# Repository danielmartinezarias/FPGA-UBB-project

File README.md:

# FPGA UBB Quantum Optics Lab
FPGA project for the control system of the OAM experiment. FPGA stores a set of images in a DDR memory, displays such images via HDMI port, prepares a train of short pulses to drive an EOM Intensity modulator, and aquires counts from 2 detectors. This project is meant to work along a GUI written in C#.

1. **electronics** contains the source files for the FMC PCB and the LM7171 AMP PCB. These includes manufacturing files, schematics and PCB outlines
2. **caja** contains a blender file with the mechanical drawings of the plastic box for the project
3. **Figuras_Hologramas_OAM** contains a set of holograms to display, and some images with numbers for calibration
4. **FPGA-Vivado-Project** contains the main Vivado project in `Genesys2_VideoDemoR1` and its sources in `srcs`. You can use the project as it is ot build the project by your own running the *srcs/Genesys2_VideoDemoR1.tcl* file with their respective dependencies and then build your own project. Synthesis, implementation and bitstream generation
5. **GUI** includes the main Graphical User Interface (GUI) to run the program along with the FPGA project. C# project in `SOFTWARE BASE-UART` and final GUI in `FINAL`. Notice that a USB UART connection is required to transmit information from the FPGA to PC 115200 buad rate.

## GUI
C# project in `GUI\SOFTWARE BASE-UART\` and FINAL Graphical User  Interface (GUI), located in `GUI\SOFTWARE BASE-UART\driver_PM_software\bin\Debug\driver_PM_software.exe`
**GUI controls**
- SOON TO BE UPDATED

## FPGA
- Main Vivado project in `FPGA-Vivado-Project\Genesys2_VideoDemoR1`, 
    - Final bitstream is located in `FPGA-Vivado-Project\Genesys2_VideoDemoR1\Genesys2_VideoDemoR1.runs\impl_1\*.bit`. 
    - You can upload this file into the FPGA using Vivado. Left bottom menu, PROGRAM AND DEBUG, Open Hardware, Auto connect, Program FPGA (with the .bit file)
- `srcs` contains all verilog files, please keep this updated

### How to use this repo?
- Create a GitHub account
- Download Github desktop
- CLONE the repository (ask me for access since it is a private repo)
    - If you want to use this files and not modify them CLONE this repository in the MAIN branch. 
    - If you want to modify it create a new branch and have fun
- Now all the files are in the folder where you cloned the repo.
- If you want to make permanet changes to the MAIN branch, make a commit, but ask me first
- GitHub is not meant to store experiment data, but code, keep this repo as clean as possible.

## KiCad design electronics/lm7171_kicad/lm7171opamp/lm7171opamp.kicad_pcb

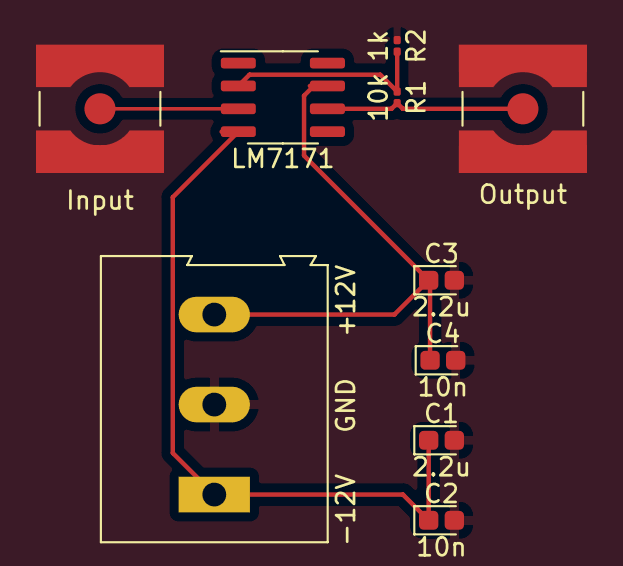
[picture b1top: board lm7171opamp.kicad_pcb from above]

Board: 2 copper layers, 10 parts (0 on the bottom side), 6 nets.

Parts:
C1, C3: 2.2u; CP_EIA-1608-08_AVX-J
C2, C4: 10n; CP_EIA-1608-08_AVX-J
J1: Input; SMA_Amphenol_132134-10_Vertical
J2: Output; SMA_Amphenol_132134-10_Vertical
J3: -12V GND +12V; TerminalBlock_Altech_AK300-3_P5.00mm
R1: 10k; R_0201_0603Metric
R2: 1k; R_0201_0603Metric
U1: LM7171; SOIC-8_3.9x4.9mm_P1.27mm

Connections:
GND: C1.2, C2.2, C3.2, C4.2, J1.2 (Ext), J2.2 (Ext), J3.2, R2.1
unnamed: J1.1 (In), U1.3 (+)
unnamed: J2.1 (In), R1.2, U1.6
unnamed: C1.1, C2.1, J3.1, U1.4 (V-)
unnamed: C3.1, C4.1, J3.3, U1.7 (V+)
unnamed: R1.1, R2.2, U1.2 (-)

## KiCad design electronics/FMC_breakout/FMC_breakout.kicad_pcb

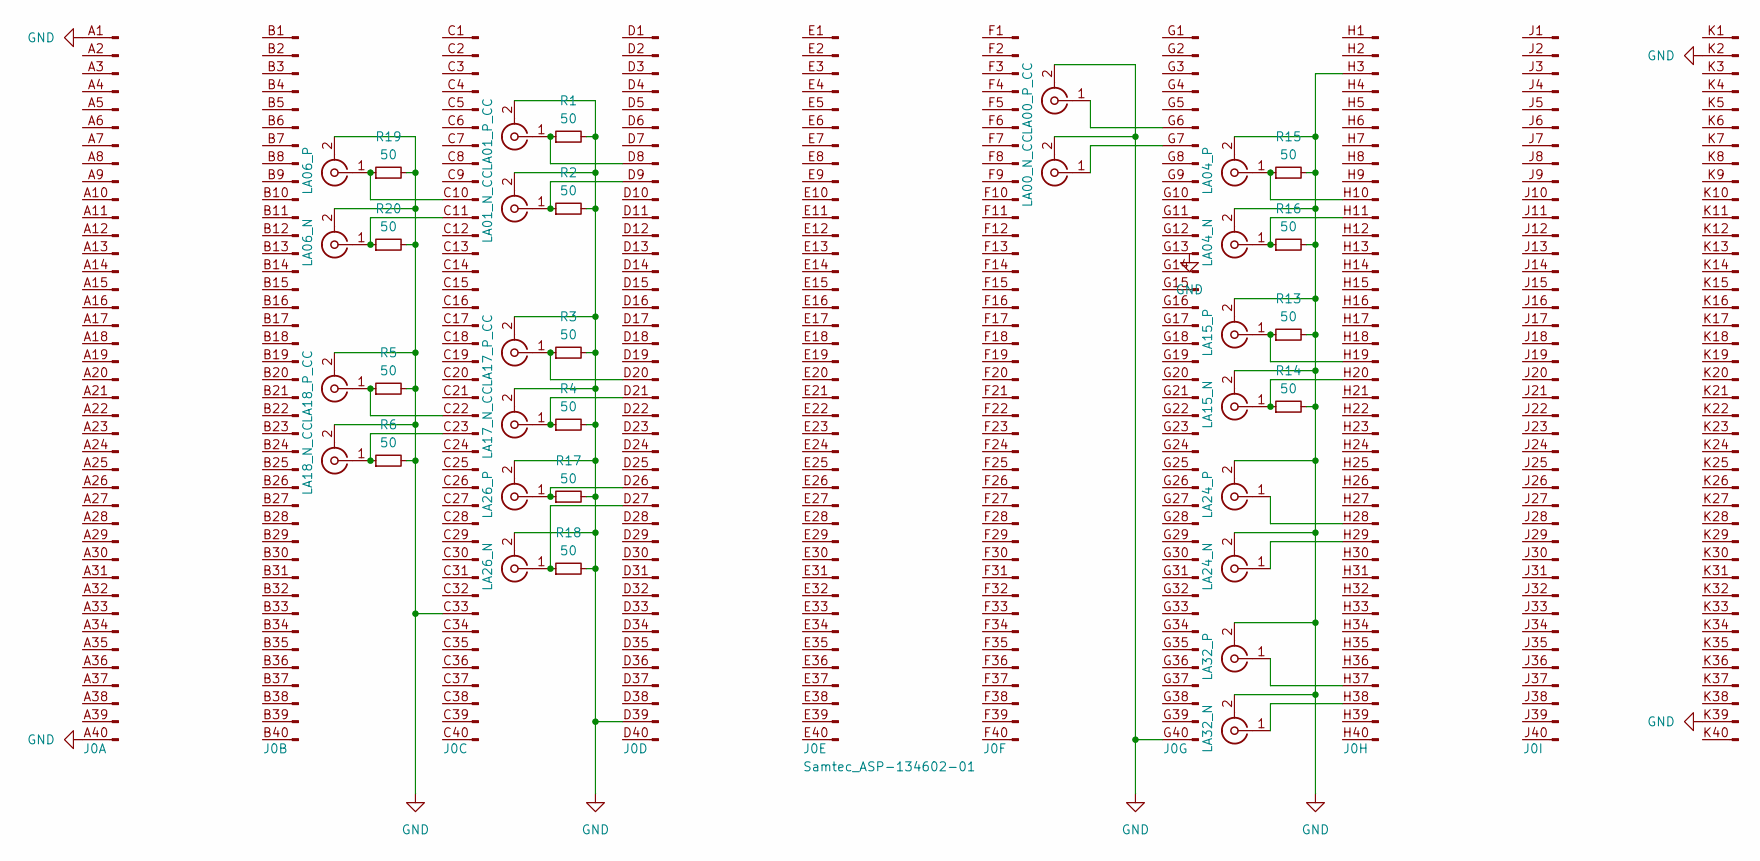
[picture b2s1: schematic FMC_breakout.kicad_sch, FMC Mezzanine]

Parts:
J0: Samtec_ASP-134602-01; Samtec_FMC_ASP-134602-01_10x40_P1.27mm_Vertical; LCSC C2875619
J1: LA01_P_CC; U.FL_Hirose_U.FL-R-SMT-1_Vertical
J2: LA01_N_CC; U.FL_Hirose_U.FL-R-SMT-1_Vertical
J3: LA17_P_CC; U.FL_Hirose_U.FL-R-SMT-1_Vertical
J4: LA17_N_CC; U.FL_Hirose_U.FL-R-SMT-1_Vertical
J5: LA18_P_CC; U.FL_Hirose_U.FL-R-SMT-1_Vertical
J6: LA18_N_CC; U.FL_Hirose_U.FL-R-SMT-1_Vertical
J7: LA00_P_CC; U.FL_Hirose_U.FL-R-SMT-1_Vertical
J8: LA00_N_CC; U.FL_Hirose_U.FL-R-SMT-1_Vertical
J9: LA32_P; U.FL_Hirose_U.FL-R-SMT-1_Vertical
J10: LA32_N; U.FL_Hirose_U.FL-R-SMT-1_Vertical
J11: LA24_P; U.FL_Hirose_U.FL-R-SMT-1_Vertical
J12: LA24_N; U.FL_Hirose_U.FL-R-SMT-1_Vertical
J13: LA15_P; U.FL_Hirose_U.FL-R-SMT-1_Vertical
J14: LA15_N; U.FL_Hirose_U.FL-R-SMT-1_Vertical
J15: LA04_P; U.FL_Hirose_U.FL-R-SMT-1_Vertical
J16: LA04_N; U.FL_Hirose_U.FL-R-SMT-1_Vertical
J17: LA26_P; U.FL_Hirose_U.FL-R-SMT-1_Vertical
J18: LA26_N; U.FL_Hirose_U.FL-R-SMT-1_Vertical
J19: LA06_P; U.FL_Hirose_U.FL-R-SMT-1_Vertical; LCSC C434812
J20: LA06_N; U.FL_Hirose_U.FL-R-SMT-1_Vertical
R1, R2, R3, R4, R5, R6, R13, R14, R15, R16, R17, R19, R20: 50; R_0402_1005Metric
R18: 50; R_0402_1005Metric; LCSC C853312

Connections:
GND: J0.A1 (Pin_1), J0.A40 (Pin_40), J0.C33 (Pin_33), J0.D39 (Pin_39), J0.G40 (Pin_40), J0.H3 (Pin_3), J0.K2 (Pin_2), J0.K39 (Pin_39), J1.2 (Ext), J2.2 (Ext), J3.2 (Ext), J4.2 (Ext), J5.2 (Ext), J6.2 (Ext), J7.2 (Ext), J8.2 (Ext), J9.2 (Ext), J10.2 (Ext), J11.2 (Ext), J12.2 (Ext), J13.2 (Ext), J14.2 (Ext), J15.2 (Ext), J16.2 (Ext), J17.2 (Ext), J18.2 (Ext), J19.2 (Ext), J20.2 (Ext), R1.2, R2.2, R3.2, R4.2, R5.2, R6.2, R13.2, R14.2, R15.2, R16.2, R17.2, R18.2, R19.2, R20.2
unnamed: J0.C10 (Pin_10), J19.1 (In), R19.1
unnamed: J0.C11 (Pin_11), J20.1 (In), R20.1
unnamed: J0.C22 (Pin_22), J5.1 (In), R5.1
unnamed: J0.C23 (Pin_23), J6.1 (In), R6.1
unnamed: J0.D8 (Pin_8), J1.1 (In), R1.1
unnamed: J0.D9 (Pin_9), J2.1 (In), R2.1
unnamed: J0.D20 (Pin_20), J3.1 (In), R3.1
unnamed: J0.D21 (Pin_21), J4.1 (In), R4.1
unnamed: J0.D26 (Pin_26), J17.1 (In), R17.1
unnamed: J0.D27 (Pin_27), J18.1 (In), R18.1
unnamed: J0.G6 (Pin_6), J7.1 (In)
unnamed: J0.G7 (Pin_7), J8.1 (In)
unnamed: J0.H10 (Pin_10), J15.1 (In), R15.1
unnamed: J0.H11 (Pin_11), J16.1 (In), R16.1
unnamed: J0.H19 (Pin_19), J13.1 (In), R13.1
unnamed: J0.H20 (Pin_20), J14.1 (In), R14.1
unnamed: J0.H28 (Pin_28), J11.1 (In)
unnamed: J0.H29 (Pin_29), J12.1 (In)
unnamed: J0.H37 (Pin_37), J9.1 (In)
unnamed: J0.H38 (Pin_38), J10.1 (In)

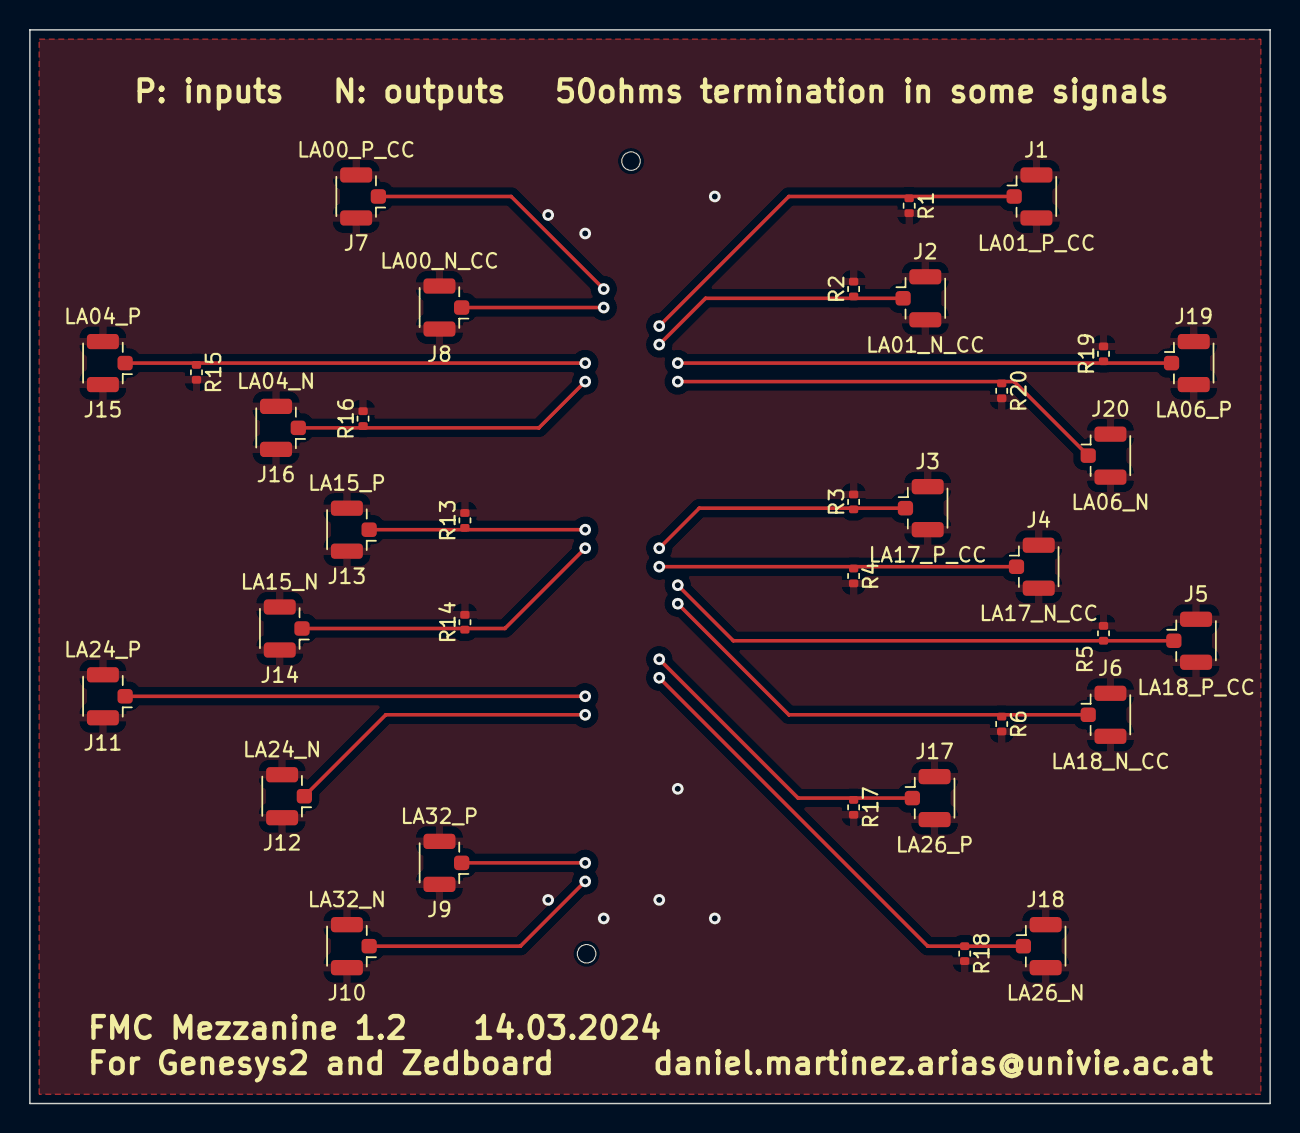
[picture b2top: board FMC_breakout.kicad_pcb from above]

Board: 2 copper layers, 85.1 x 73.7 mm, 35 parts (1 on the bottom side), 21 nets.

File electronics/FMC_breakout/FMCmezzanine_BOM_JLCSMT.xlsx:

Comment | Designator | Footprint | JLCPCB Part #（optional）
50ohm | R1,R2,R3,R4,R5,R6,R13,R14,R15,R16,R17,R18,R19,R20 | R_0402_1005Metric | C853312
 | J1,J2,J3,J4,J5,J6,J7,J8,J9,J10,J11,J12,J13,J14,J15,J16,J17,J18,J19,J20 | Connector_Coaxial:U.FL_Hirose_U.FL-R-SMT-1_Vertical | C434812
Samtec_ASP-134602-01 | J0 | Connector_Samtec:Samtec_FMC_ASP-134602-01_10x40_P1.27mm_Vertical | C2875619

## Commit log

2024-05-09 Initial project commit
    To set up the project.
    Main FPGA connection:
    fmc_la_p_00 <= sync;
    fmc_la_p_18 <= pulse;
    fmc_la_p_24 <= trigger_out;
    sync_ext <= fmc_la_p_32;
2024-05-28 Laser control
    Added laser control in sync_pulse_det_generator.v, its dependencies and GUI. Signal CW enables a continuous emission from the MZI, pulse_control enables the pulse
2024-06-28 det and sync
    -Major bug fixes
    -Laser control buttons
    -Data Adquisition from Det0 and Det1
    -Synchronization in between Alice and Bob
    -New lm7171 pcb
2024-07-01 signal det bug
    renaming signals bug fixed
2024-07-23 projectman
    rearrangement of the folders and real vivado project
2024-07-23 dll_route0
    added a \ in the dll route
2024-07-23 dll_path
    corrected path
2024-07-24 det to pin_04
    Hice un cambio del pin 24 (det) al pin 04
2024-07-24 det to pin 04
    Genere el bitstream para el cambio del pulso det al pin 04
2024-07-25 RampFix
    Ramp fix and sync
2024-07-25 sync master
    Control DM estaba usando el sync_internal siempre, debido a que sync_pulse_det tenia como output sync y no sync_master... resuleto
2024-07-28 deleted blinking LEDs
    Now only LED 0 is connected to a signal. It has sync, so it serves as Alice/Bob identifier. Alice should be always blinking while Bob only blinks when he receives a signal from Alice
2024-07-31 alice and bob no sw
    added control in gui for alice and bob
2024-07-31 Bitstream 31/07
    Creación del Bitstream para nuevas pruebas.
2024-08-21 fmc_32 -> fmc_15
    Hola cambie el puerto fmc_la_p_32 al puerto fmc_la_p_15 para el sync externo de Bob
2024-08-21 Fmc_15 -> Fmc_0_n
    Cambie el puerto de Bob (sync_ext) de fmc_15 al fmc_0_n, elegimos este por que no tiene una resistencia de 50 ohms
2024-09-05 Paso Delay a incremento de 5ns
    Cambie el incremento de saltos de 50 ns a saltos de 5 ns
2024-09-06 det0 to 3V3
    changed the standard in the .xdc file
2024-09-16 Changes in Vivado
    -Cambie parte del codigo de AccCuentas.v, lo que estaba antes lo deje comentado
    - Y en el top (Genesys2_VideoDemoR1.vhd) deje comentado la señal que no estamos ocupando que en este caso es EN que viene de AccCuentas
2024-09-22 idqube
    idqube detector added
2024-09-23 idqube_V2
2024-09-24 newDet0 port
    la01_p to LA32_P
2024-09-24 Bitstream pin 32
    Genere el bitstream para el cambio del det 0, decidimos que ingresara a Bob por el pin 32 ya que este no posee una resistencia.
2024-10-05 idqube_V2
    fixed bugs on AccCuentas. Deje conectado el clk a det1
2024-10-08 Generacion BitStream
    Generacion del bitstream para poder solucionar el problema de oneshoot (creemos que es el culpable de que las cuentas en el fpga no se actualicen)
2024-10-25 Solucion Error AccCuentas
    Encontre algunos errores en la AccCuentas que arregle, faltaba declarar algunas variables
2024-10-25 Bitstream con correcion de error AccCuentas
    Genere de nuevo el bitstream, arregle algunas variables que no estaban definidas
2025-02-12 testsCristobalVienna12.02
    usamos genesys en univie, Alice, vimos una senal en cuentas pero es erronea
2025-03-04 Creation of 4 new signals
2025-03-04 Add button for signals
2025-03-04 Test
2025-03-04 Test 2
2025-03-04 Test 3
2025-03-04 Test4
2025-03-04 Test5
2025-03-04 test 5
2025-03-04 Test 6
2025-03-04 test 7
2025-03-05 test 8
2025-03-05 Test succesfully
2025-03-05 Test F
2025-03-05 test 10
2025-03-10 Test Delays
2025-03-11 Add control phase
2025-03-11 Add Control Phase v2
2025-03-12 Test complete PS
2025-03-13 Test and add label (change ns)
2025-03-19 Test UBB
2025-03-19 Funcionamiento Correcto (Cuentas)
2025-03-19 add control_phase.v
2025-03-21 Test UBB 2
2025-03-21 mzi and det independent freq
2025-03-21 MZI syncrho
2025-03-21 Test mzi_det
2025-03-24 UBB test Cuentas
2025-04-01 amp_test
2025-04-01 add new output
    Agregue n_18 como MZI y p_24 como Sync para el monitoreo usando un osciloscopio
2025-05-19 Bitstream cambio Mzi
2025-05-19 Correcion puerto mzi
    Cambio del puerto mzi
2025-05-20 Mediciones
2025-05-20 Cambio mediciones formato texto
2025-05-20 Software Medicion txt
2025-05-20 Sotftware medicion
2025-05-20 sotfware medicion
2025-06-09 change port
2025-06-10 test_bitstream
2025-06-10 Prueba Bitstream
2025-06-10 2 prueba bitstream
2025-06-10 change port MZI
2025-06-10 mzi solucionado
2026-01-14 sync change
2026-01-14 Asignacion CW y signal pulse Control
    signal pulse_control : std_logic := '1';
    signal CW : std_logic := '0';
    Forzar controles a constantes
2026-01-14 Cambio LCVMOS FMC 1.2 -> 3.3V
